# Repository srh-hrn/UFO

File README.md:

# UFO

Hallo :)
Hier ein kurzer Überblick zu meinem Projekt:

Den Schaltkreis habe ich bereits ausprobiert und schon ein bisschen gelötet und er funktioniert soweit sehr gut. Ein Video davon habe ich im Wiki hochgeladen.

Folgende 20 Fehler treten momentan im DRC auf:

1 - 7 Clearance Violation: bei Durchkontaktierungen für LEDs auf Fcu, allerdings nicht bei allen. Manche konnte ich durch Verschieben in Millimeterschritten korrigieren. Ich werde versuchen, die restlichen Fehler genauso zu beseitigen, aber wahrscheinlich schränken diese die Funktion des PCBs gar nicht ein.

8 - 19 Footprint has malformed courtyard (not a closed shape): Dieser Fehler tritt an mehreren Stellen eines Footprints auf, den ich in der library gefunden habe. Zoomt man an die markierten Stellen dich heran, sind kleine Ausbuchtungen der geraden Linien zu erkennen. Die Zeichnung ist also lediglich nicht ganz sauber, der Footprint jedoch vollständig und geschlossen.

20 Silkscreen clipped by solder mask: Das betrifft eine kleine Stelle am Ufo. Ich habe dort eine Weile ausprobiert, wie ich die Linien ziehe, damit sie zwar geschlossen sind, aber nichts überschneiden. Letztendlich gibt es einen Berührungspunkt, da die Linie abgerundet ist, aber ich denke, das sollte kein Problem sein.

Danke fürs Drüberschauen!

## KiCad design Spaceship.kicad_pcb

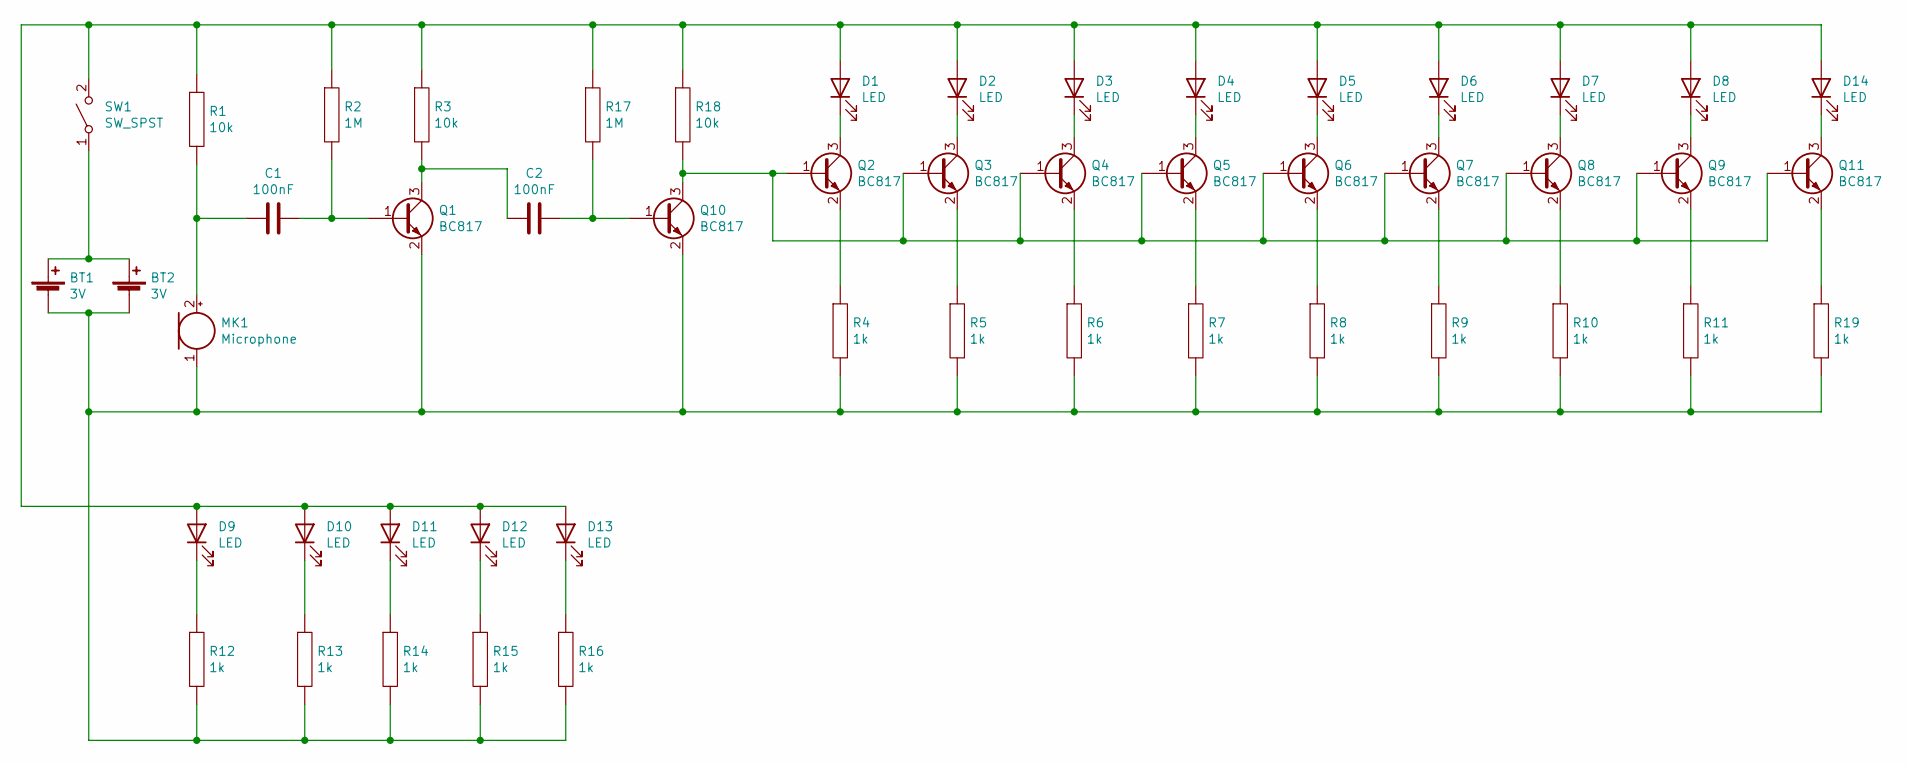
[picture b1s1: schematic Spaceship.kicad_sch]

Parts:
BT1, BT2: 3V; BatteryHolder_Keystone_3008_1x2450
C1, C2: 100nF; C_1210_3225Metric_Pad1.33x2.70mm_HandSolder
D1, D2, D3, D4, D5, D6, D7, D8, D9, D10, D11, D12, D13, D14: LED; LED_1206_3216Metric_ReverseMount_Hole1.8x2.4mm
MK1: Microphone
Q1, Q2, Q3, Q4, Q5, Q6, Q7, Q8, Q9, Q10, Q11: BC817; SOT-23
R1, R3, R18: 10k; R_1210_3225Metric_Pad1.30x2.65mm_HandSolder
R2, R17: 1M; R_1210_3225Metric_Pad1.30x2.65mm_HandSolder
R4, R5, R6, R7, R8, R9, R10, R11, R12, R13, R14, R15, R16, R19: 1k; R_1210_3225Metric_Pad1.30x2.65mm_HandSolder
SW1: SW_SPST; SW_SPDT_PCM12

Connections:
unnamed: C1.1, MK1.2 (+), R1.2
unnamed: C1.2, Q1.1 (B), R2.2
unnamed: C2.1, Q1.3 (C), R3.2
unnamed: C2.2, Q10.1 (B), R17.2
unnamed: D1.1 (K), Q2.3 (C)
unnamed: D1.2 (A), D2.2 (A), D3.2 (A), D4.2 (A), D5.2 (A), D6.2 (A), D7.2 (A), D8.2 (A), D9.2 (A), D10.2 (A), D11.2 (A), D12.2 (A), D13.2 (A), D14.2 (A), R1.1, R2.1, R3.1, R17.1, R18.1, SW1.2 (B)
unnamed: D2.1 (K), Q3.3 (C)
unnamed: D3.1 (K), Q4.3 (C)
unnamed: D4.1 (K), Q5.3 (C)
unnamed: D5.1 (K), Q6.3 (C)
unnamed: D6.1 (K), Q7.3 (C)
unnamed: D7.1 (K), Q8.3 (C)
unnamed: D8.1 (K), Q9.3 (C)
unnamed: D9.1 (K), R12.1
unnamed: D10.1 (K), R13.1
unnamed: D11.1 (K), R14.1
unnamed: D12.1 (K), R15.1
unnamed: D13.1 (K), R16.1
unnamed: D14.1 (K), Q11.3 (C)
unnamed: BT1.2 (-), BT2.2 (-), MK1.1 (-), Q1.2 (E), Q10.2 (E), R4.2, R5.2, R6.2, R7.2, R8.2, R9.2, R10.2, R11.2, R12.2, R13.2, R14.2, R15.2, R16.2, R19.2
unnamed: Q2.2 (E), R4.1
unnamed: Q3.2 (E), R5.1
unnamed: Q4.2 (E), R6.1
unnamed: Q5.2 (E), R7.1
unnamed: Q6.2 (E), R8.1
unnamed: Q7.2 (E), R9.1
unnamed: Q8.2 (E), R10.1
unnamed: Q9.2 (E), R11.1
unnamed: Q2.1 (B), Q3.1 (B), Q4.1 (B), Q5.1 (B), Q6.1 (B), Q7.1 (B), Q8.1 (B), Q9.1 (B), Q10.3 (C), Q11.1 (B), R18.2
unnamed: Q11.2 (E), R19.1
unnamed: BT1.1 (+), BT2.1 (+), SW1.1 (A)

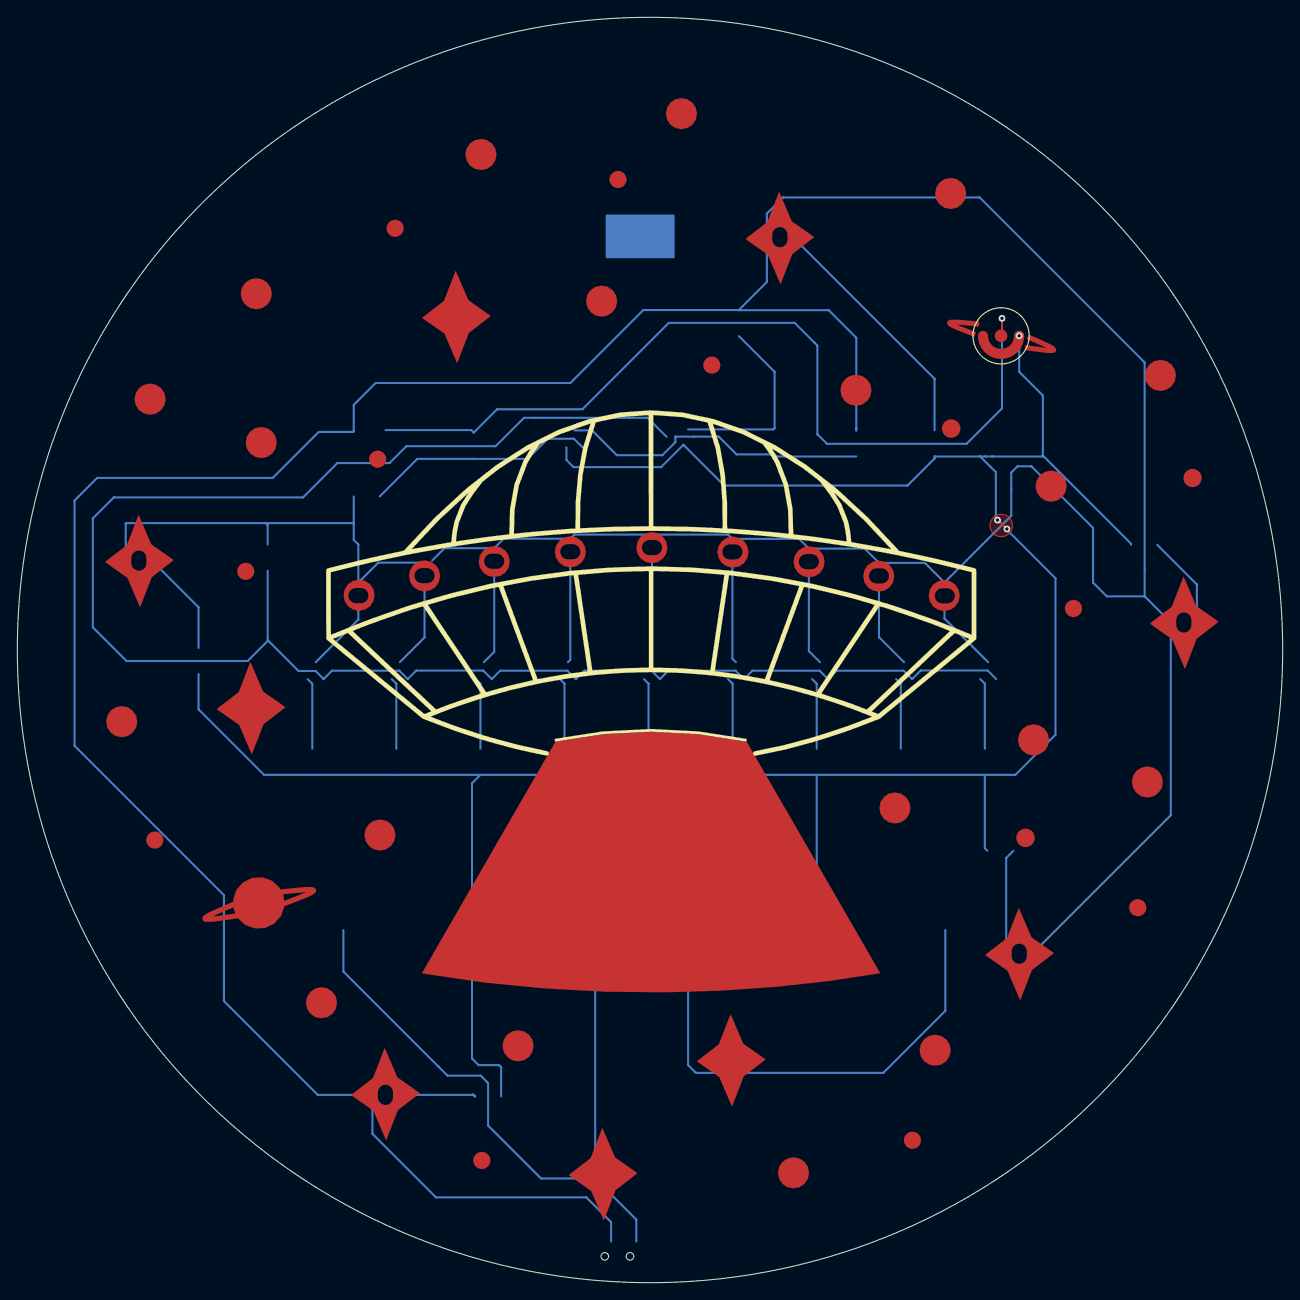
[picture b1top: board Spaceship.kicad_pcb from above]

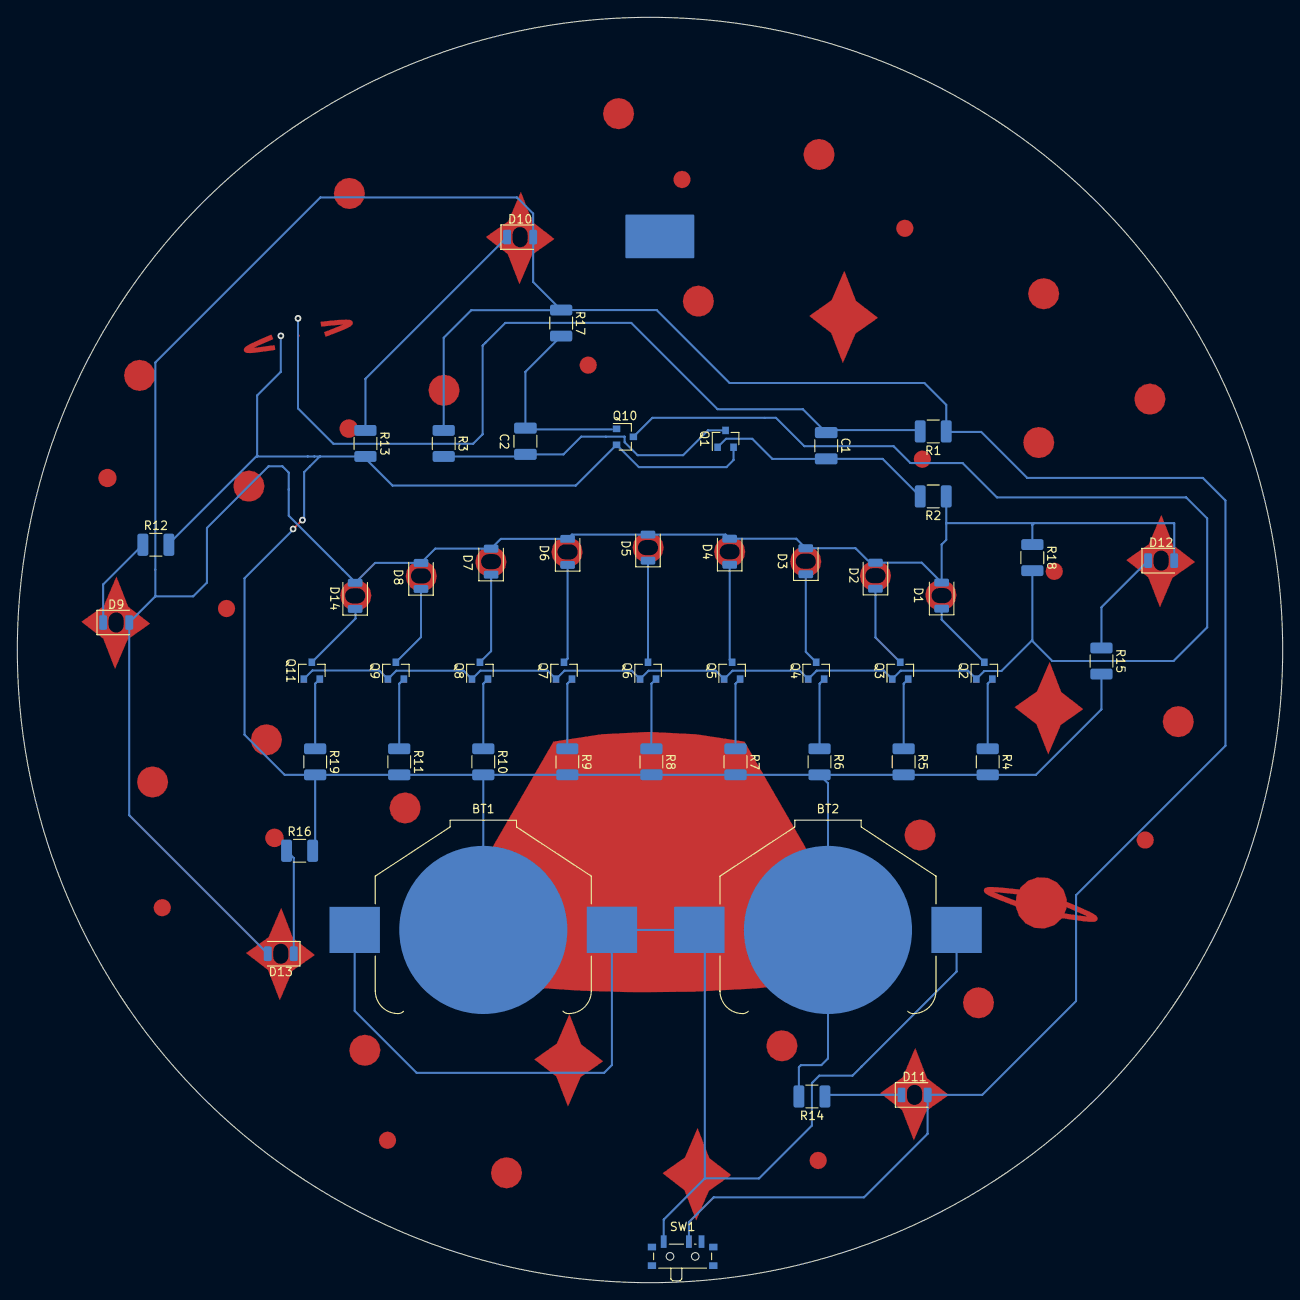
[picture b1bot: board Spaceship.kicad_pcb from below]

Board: 2 copper layers, 150.5 x 150.5 mm, 51 parts (49 on the bottom side), 31 nets.

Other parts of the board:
Ref**: Val**; UFO
